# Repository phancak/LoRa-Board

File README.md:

# STM32WL55CCU6 LoRa Expansion Board  

## 📑 Quick Access
* [**📂 View Project Schematics (PDF)**](./Schematics/LoRa_Board_Schematics.pdf)

## Overview  
This project features a **LoRa expansion board** based on the **STM32WL55CCU6 MCU**, designed to provide long-range, low-power wireless communication for embedded systems. With support for **I2C**, **UART**, and **SPI** communication interfaces, this board is ideal for integrating **LoRa** functionality into larger projects, enabling **reliable, long-range data transmission** in applications like **IoT** and **industrial automation**. The STM32WL55CCU6 offers an energy-efficient solution for **wireless connectivity** in remote or challenging environments.

## Features  
- **STM32WL55CCU6 MCU** – Ultra-low-power, LoRa-capable microcontroller  
- **LoRa Communication** – Long-range, low-power wireless protocol  
- **I2C, UART, SPI Interfaces** – Multiple communication options for flexibility  
- **Low Power Operation** – Ideal for battery-operated and remote applications  
- **Compact Design** – Easily integratable into various embedded systems  

## Applications  
- **IoT Networks** – Connecting sensors and devices over long distances  
- **Smart Agriculture** – Wireless communication for monitoring systems  
- **Asset Tracking** – Real-time location data transmission in logistics  
- **Industrial Automation** – Reliable wireless control and monitoring systems  

## Getting Started  
### Hardware Requirements  
- STM32WL55CCU6 LoRa Expansion Board  
- Host MCU (e.g., STM32, ESP32, Raspberry Pi, etc.)  
- Power Supply (3.3V)  
- USB-to-Serial Debugging Tools  

### Software Requirements  
- **STM32CubeIDE** – Development environment for firmware  
- **LoRaWAN Libraries** – LoRa communication protocol support  
- **ST-Link or J-Link** – Debugging and flashing tools  

## Setup & Usage  
1. **Power the Board** – Provide 3.3V to the board.  
2. **Connect to Host MCU** – Use I2C, UART, or SPI to interface with the board.  
3. **Flash Firmware** – Upload firmware for LoRa communication.  
4. **Start Transmitting** – Send and receive long-range data using LoRa.

## Repository Structure  
/Hardware - PCB schematics and design files
/Schematic - Circuit diagrams (PDF, KiCad, Altium, etc.)
/PCB - Board layout files (Gerber, BOM, assembly files)

## Future Enhancements  
- 🔹 **Advanced Power Management** – Further optimization for ultra-low-power operation  
- 🔹 **Multi-Channel Support** – Enable simultaneous communication across multiple LoRa channels  
- 🔹 **Secure Communication** – Integrate encryption for data security  

## License  
This project is open-source under the **MIT License**.

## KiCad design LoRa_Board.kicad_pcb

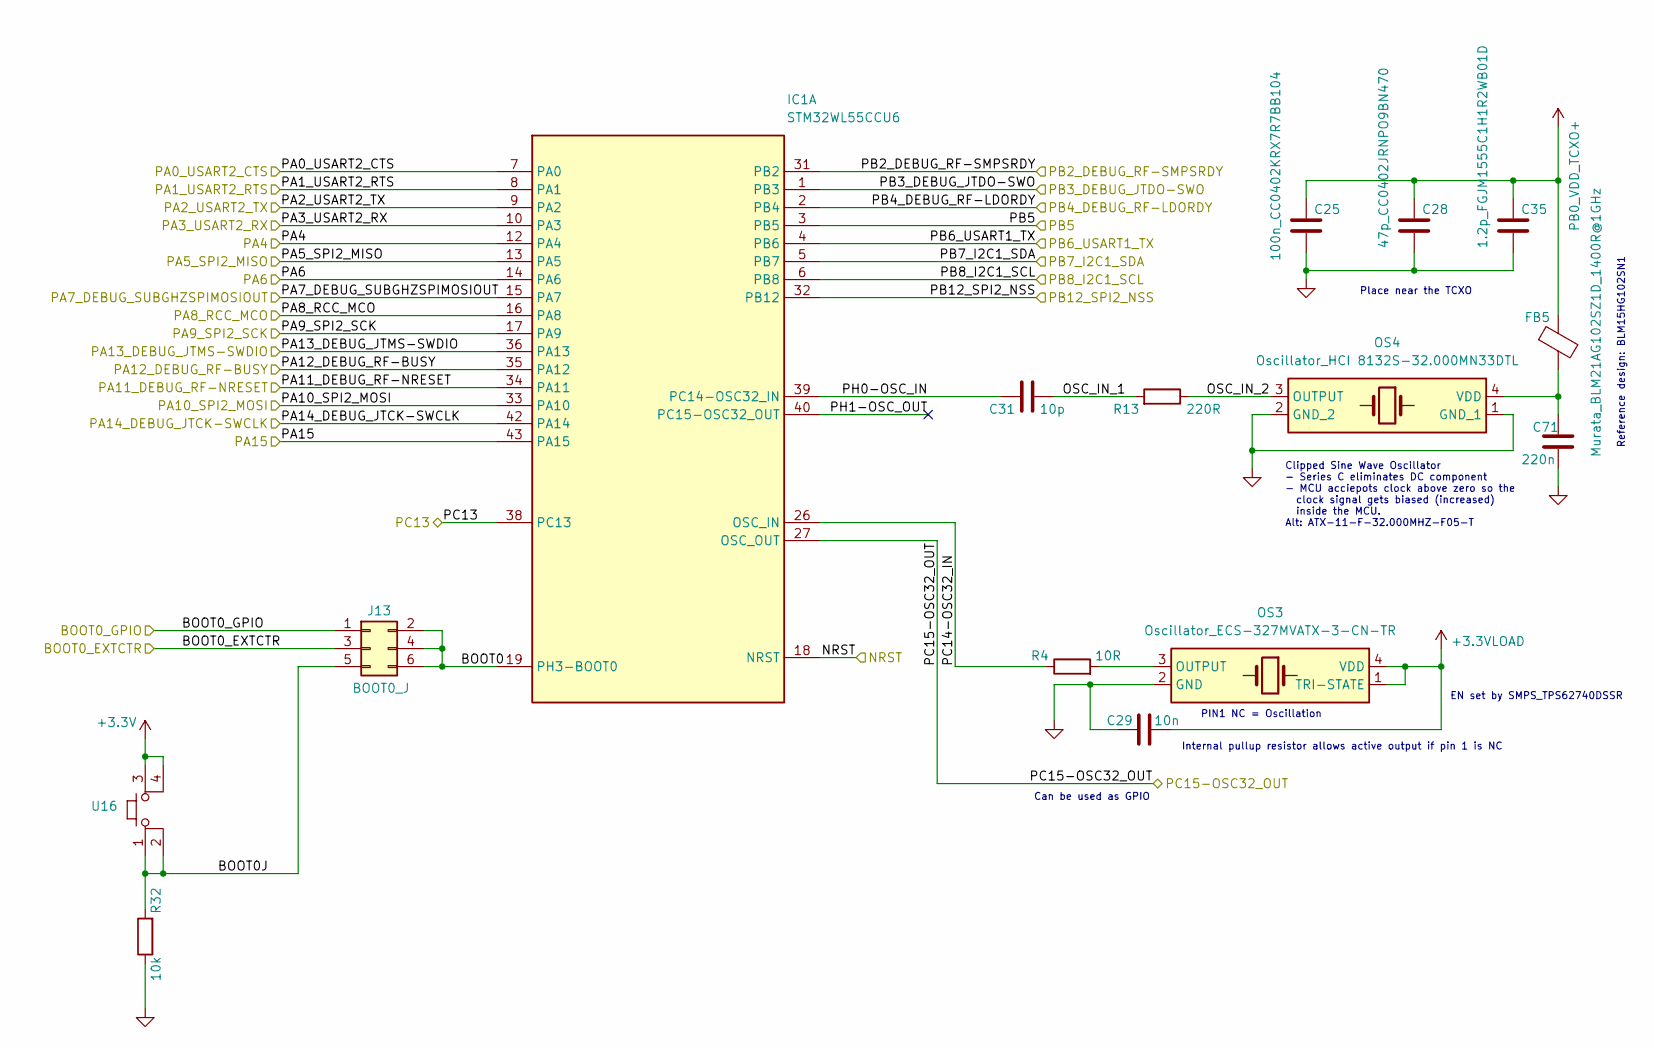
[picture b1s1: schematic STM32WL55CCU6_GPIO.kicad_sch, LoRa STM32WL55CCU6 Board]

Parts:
C25: 100n_CC0402KRX7R7BB104; C_0603_1608Metric
C28: 47p_CC0402JRNPO9BN470; C_0603_1608Metric
C29: 10n; C_0603_1608Metric
C31: 10p; C_0603_1608Metric
C35: 1.2p_FGJM1555C1H1R2WB01D; C_0603_1608Metric
C71: 220n; C_0603_1608Metric
FB5: Murata_BLM21AG102SZ1D_1400R@1GHz; C_0805_2012Metric
IC1: STM32WL55CCU6; STM32WL55CCU6_QFN50P700X700X65-49N-D; Manufacturer_Part_Number STM32WL55CCU6; Mouser Part Number 511-STM32WL55CCU6
J13: BOOT0_J; PinHeader_2x03_P2.54mm_Vertical
OS3: Oscillator_ECS-327MVATX-3-CN-TR; Crystal_SMD_3225-4Pin_3.2x2.5mm; Mouser Part Number 520-327MVATX-3-CNT
OS4: Oscillator_HCI 8132S-32.000MN33DTL; Crystal_SMD_3225-4Pin_3.2x2.5mm; Mouser Part Number 520-TXO32CSMV320ANTR
R4: 10R; R_0603_1608Metric
R13: 220R; R_0603_1608Metric
R32: 10k; R_0805_2012Metric
U16: Button_SKSCLCE010

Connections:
+3.3V: U16.3, U16.4; also elsewhere on the board
+3.3VLOAD: C29.2, OS3.1 (TRI-STATE), OS3.4 (VDD); also elsewhere on the board
/Interfaces/I2C_SCL_HDR_0: IC1.6 (PB8); also elsewhere on the board
/Interfaces/I2C_SDA_HDR_0: IC1.5 (PB7); also elsewhere on the board
/Interfaces/I/O_HDR0: J13.1; also elsewhere on the board
/Interfaces/I/O_HDR1: IC1.8 (PA1); also elsewhere on the board
/Interfaces/I/O_HDR2: IC1.15 (PA7); also elsewhere on the board
/Interfaces/I/O_HDR3: IC1.16 (PA8); also elsewhere on the board
/Interfaces/I/O_HDR4: IC1.43 (PA15); also elsewhere on the board
/Interfaces/I/O_HDR5: IC1.38 (PC13); also elsewhere on the board
/Interfaces/I/O_HDR6: IC1.34 (PA11); also elsewhere on the board
/Interfaces/I/O_HDR7: IC1.31 (PB2); also elsewhere on the board
/Interfaces/I/O_HDR8: IC1.35 (PA12); also elsewhere on the board
/Interfaces/I/O_HDR9: IC1.2 (PB4); also elsewhere on the board
/Interfaces/I/O_HDR10: IC1.7 (PA0); also elsewhere on the board
/Interfaces/SPI_CLK: IC1.17 (PA9); also elsewhere on the board
/Interfaces/SPI_CS: IC1.32 (PB12); also elsewhere on the board
/Interfaces/SPI_MISO: IC1.13 (PA5); also elsewhere on the board
/Interfaces/SPI_MOSI: IC1.33 (PA10); also elsewhere on the board
/Interfaces/UART1_TX/RX: IC1.4 (PB6); also elsewhere on the board
/Power_Management/BFR_RST: IC1.18 (NRST); also elsewhere on the board
/Power_Management/CTRL: IC1.3 (PB5); also elsewhere on the board
/STM32WL55CCU6_GPIO/BOOT0: IC1.19 (PH3-BOOT0), J13.2, J13.4, J13.6
/STM32WL55CCU6_GPIO/BOOT0J: J13.5, R32.2, U16.1, U16.2
/STM32WL55CCU6_GPIO/BOOT0_EXTCTR: J13.3; also elsewhere on the board
/STM32WL55CCU6_GPIO/OSC_IN_1: C31.1, R13.2
/STM32WL55CCU6_GPIO/OSC_IN_2: OS4.3 (OUTPUT), R13.1
/STM32WL55CCU6_GPIO/PA2_USART2_TX: IC1.9 (PA2); also elsewhere on the board
/STM32WL55CCU6_GPIO/PA3_USART2_RX: IC1.10 (PA3); also elsewhere on the board
/STM32WL55CCU6_GPIO/PA4: IC1.12 (PA4); also elsewhere on the board
/STM32WL55CCU6_GPIO/PA6: IC1.14 (PA6); also elsewhere on the board
/STM32WL55CCU6_GPIO/PA13_DEBUG_JTMS-SWDIO: IC1.36 (PA13); also elsewhere on the board
/STM32WL55CCU6_GPIO/PA14_DEBUG_JTCK-SWCLK: IC1.42 (PA14); also elsewhere on the board
/STM32WL55CCU6_GPIO/PB3_DEBUG_JTDO-SWO: IC1.1 (PB3); also elsewhere on the board
/STM32WL55CCU6_GPIO/PC14-OSC32_IN: IC1.26 (OSC_IN), R4.1
/STM32WL55CCU6_GPIO/PC15-OSC32_OUT: IC1.27 (OSC_OUT); also elsewhere on the board
/STM32WL55CCU6_GPIO/PH0-OSC_IN: C31.2, IC1.39 (PC14-OSC32_IN)
/STM32WL55CCU6_GPIO/PH1-OSC_OUT: IC1.40 (PC15-OSC32_OUT)
GND: C25.2, C28.2, C29.1, C35.2, C71.1, OS3.2 (GND), OS4.1 (GND_1), OS4.2 (GND_2), R32.1; also elsewhere on the board
unnamed: OS3.3 (OUTPUT), R4.2
unnamed: C71.2, FB5.2, OS4.4 (VDD)
PB0_VDD_TCXO+: C25.1, C28.1, C35.1, FB5.1; also elsewhere on the board

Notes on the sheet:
Internal pullup resistor allows active output if pin 1 is NC
PIN1 NC = Oscillation
Clipped Sine Wave Oscillator - Series C eliminates DC component - MCU acciepots clock above zero so the clock signal gets biased (increased) inside the MCU. Alt: ATX-11-F-32.000MHZ-F05-T
EN set by SMPS_TPS62740DSSR
Place near the TCXO
Can be used as GPIO
Reference design: BLM15HG102SN1

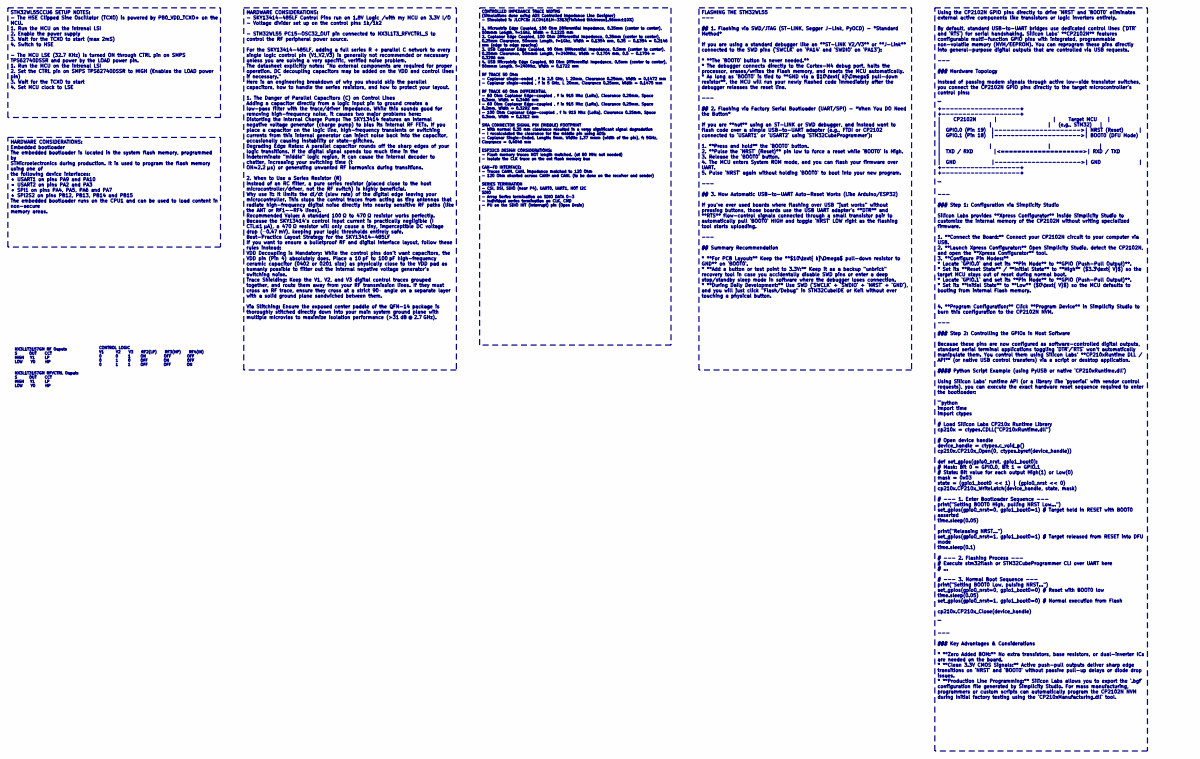
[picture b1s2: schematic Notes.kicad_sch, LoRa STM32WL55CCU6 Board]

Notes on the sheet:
CONTROL LOGIC V1 V2 V3 RF2(LP) RF3(HP) RF4(IN) 0 0 1 ON OFF OFF 0 1 0 OFF ON OFF 0 1 1 OFF OFF ON
NX3L1T3157GM RF Ouputs S OUT CCT HIGH Y1 LP LOW Y0 HP
NX3L1T3157GM RFVCTRL Ouputs S OUT CCT HIGH Y1 LP LOW Y0 HP
FLASHING THE STM32WL55 --- ## 1. Flashing via SWD/JTAG (ST-LINK, Segger J-Link, PyOCD) - *Standard Method* If you are using a standard debugger like an **ST-LINK V2/V3** or **J-Link** connected to the SWD pins (`SWCLK` on `PA14` and `SWDIO` on `PA13`): * **The `BOOT0` button is never needed.** * Th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
Using the CP2102N GPIO pins directly to drive `NRST` and `BOOT0` eliminates external active components like transistors or logic inverters entirely. By default, standard USB-to-UART bridges use dedicated control lines (`DTR` and `RTS`) for serial handshaking. Silicon Labs' **CP2102N** features conf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
CONTROLLED IMPEDANCE TRACE WIDTHS (Simulations done using ADS Controlled Impedance Line Designer) - Simulated is JLCPCB: JLC04161H-3313(Finished thickness1.56mm±10%) 1. Microstrip Edge Coupled, 100 Ohm Differential Impedance, 0.35mm (center to center), 50mmm Length, f=1Ghz, Width = 0.1225 mm 2. Cop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
HARDWARE CONSIDERATIONS: - SKY13414-485LF Control Pins run on 1.8V Logic /with my MCU on 3.3V I/O - Voltage divider set up on the control pins 1k/1k2 - STM32WL55 PC15-OSC32_OUT pin connected to NX3L1T3_RFVCTRL_S to control the RF peripheral power source. For the SKY13414-485LF, adding a full series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
STM32WL55CCU6 SETUP NOTES: - The HSE Clipped Sine Oscillator (TCXO) is powered by PB0_VDD_TCXO+ on the MCU. 1. Run the MCU on the intrenal LSI 2. Enable the power supply 3. Wait for the TCXO to start (max 2mS) 4. Switch to HSE - The MCU LSE (32.7 KHz) is turned ON through CTRL pin on SMPS TPS62740D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
HARDWARE CONSIDERATIONS: Embedded bootloader The embedded bootloader is located in the system flash memory, programmed by STMicroelectronics during production. It is used to program the flash memory using one of the following device interfaces: • USART1 on pins PA9 and PA10 • USART2 on pins PA2 and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

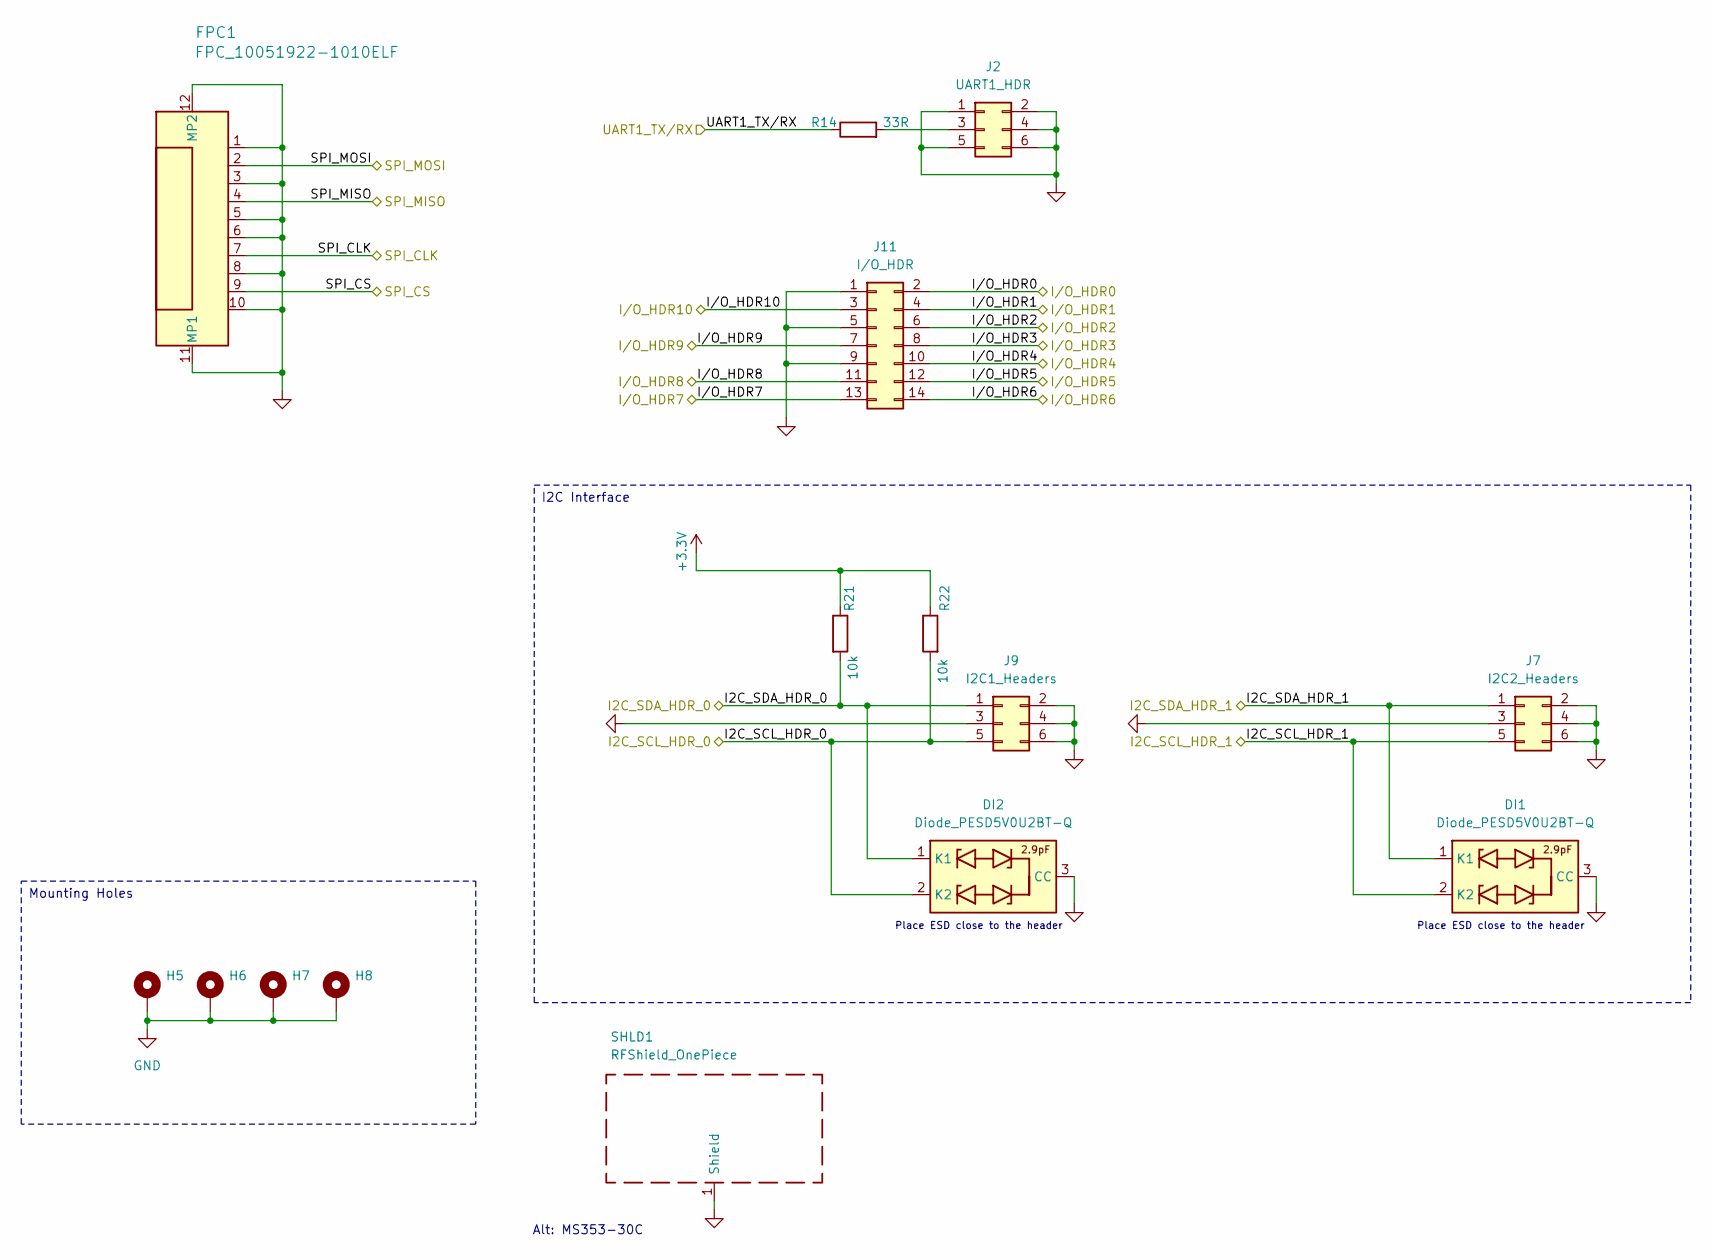
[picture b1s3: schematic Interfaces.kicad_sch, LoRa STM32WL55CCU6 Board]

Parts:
DI1, DI2: Diode_PESD5V0U2BT-Q; SOT-23; Manufacturer_Part_Number BZX84C6V2-7-F; Mouser Part Number 621-BZX84C6V2-F
FPC1: FPC_10051922-1010ELF; FPC_10051922_1010
H5, H6, H7, H8: MountingHole_Pad; MountingHole_3.2mm_M3_Pad
J2: UART1_HDR; PinHeader_2x03_P2.54mm_Horizontal_Court
J7: I2C2_Headers; PinHeader_2x03_P2.54mm_Horizontal_Court
J9: I2C1_Headers; PinHeader_2x03_P2.54mm_Horizontal_Court
J11: I/O_HDR; PinHeader_2x07_P2.54mm_Horizontal
R14: 33R; R_0603_1608Metric
R21, R22: 10k; R_0805_2012Metric
SHLD1: RFShield_OnePiece; RFSHIELD_MS353-30F

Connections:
+3.3V: R21.1, R22.1; also elsewhere on the board
/Interfaces/I2C_SCL_HDR_0: DI1.2 (K2), DI2.2 (K2), J7.5, J9.5, R22.2; also elsewhere on the board
/Interfaces/I2C_SDA_HDR_0: DI1.1 (K1), DI2.1 (K1), J7.1, J9.1, R21.2; also elsewhere on the board
/Interfaces/I/O_HDR0: J11.2; also elsewhere on the board
/Interfaces/I/O_HDR1: J11.4; also elsewhere on the board
/Interfaces/I/O_HDR2: J11.6; also elsewhere on the board
/Interfaces/I/O_HDR3: J11.8; also elsewhere on the board
/Interfaces/I/O_HDR4: J11.10; also elsewhere on the board
/Interfaces/I/O_HDR5: J11.12; also elsewhere on the board
/Interfaces/I/O_HDR6: J11.14; also elsewhere on the board
/Interfaces/I/O_HDR7: J11.13; also elsewhere on the board
/Interfaces/I/O_HDR8: J11.11; also elsewhere on the board
/Interfaces/I/O_HDR9: J11.7; also elsewhere on the board
/Interfaces/I/O_HDR10: J11.3; also elsewhere on the board
/Interfaces/SPI_CLK: FPC1.7; also elsewhere on the board
/Interfaces/SPI_CS: FPC1.9; also elsewhere on the board
/Interfaces/SPI_MISO: FPC1.4; also elsewhere on the board
/Interfaces/SPI_MOSI: FPC1.2; also elsewhere on the board
/Interfaces/UART1_TX/RX: R14.1; also elsewhere on the board
GND: DI1.3 (CC), DI2.3 (CC), FPC1.1, FPC1.3, FPC1.5, FPC1.6, FPC1.8, FPC1.10, FPC1.11 (MP1), FPC1.12 (MP2), H5.1 (1_1), H6.1 (1_1), H7.1 (1_1), H8.1 (1_1), J2.1, J2.2, J2.4, J2.5, J2.6, J7.2, J7.3, J7.4, J7.6, J9.2, J9.3, J9.4, J9.6, J11.1, J11.5, J11.9, SHLD1.1 (Shield_1); also elsewhere on the board
unnamed: J2.3, R14.2

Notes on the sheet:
Place ESD close to the header
Alt: MS353-30C
I2C Interface
Mounting Holes

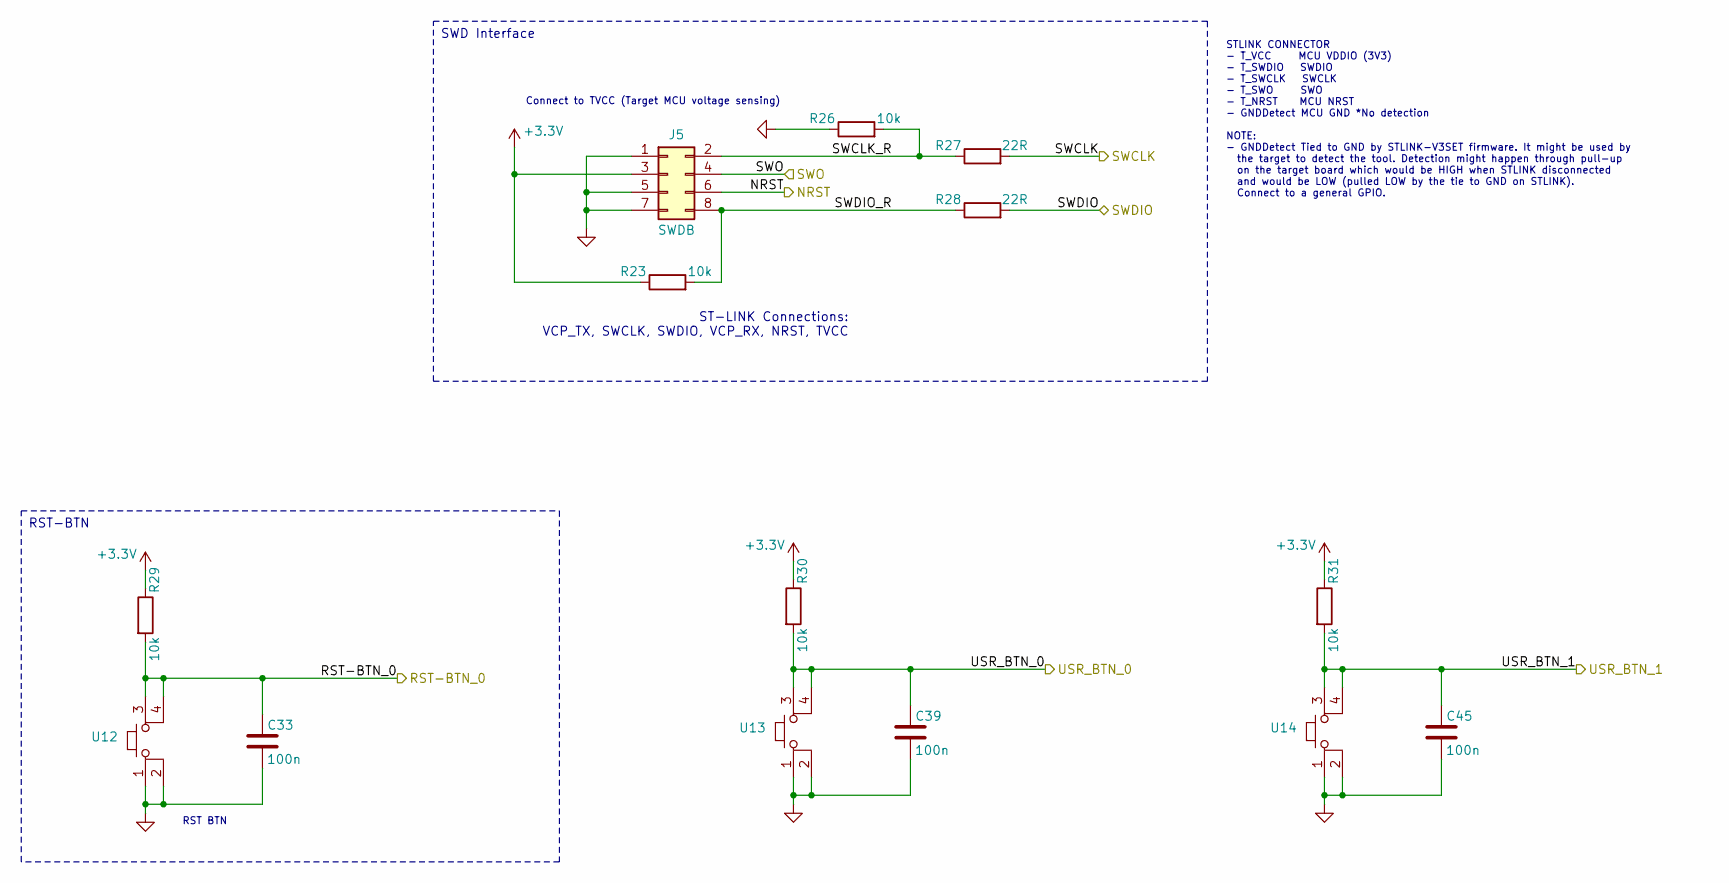
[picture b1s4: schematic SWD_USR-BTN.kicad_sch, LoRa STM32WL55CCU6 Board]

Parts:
C33, C39, C45: 100n; C_0603_1608Metric
J5: SWDB; PinHeader_2x04_P2.54mm_Horizontal
R23, R26: 10k; R_0603_1608Metric
R27, R28: 22R; R_0603_1608Metric
R29, R30, R31: 10k; R_0805_2012Metric
U12, U13, U14: Button_SKSCLCE010

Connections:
+3.3V: J5.3, R23.1, R29.1, R30.1, R31.1; also elsewhere on the board
/Interfaces/I/O_HDR6: C39.2, R30.2, U13.3, U13.4; also elsewhere on the board
/Interfaces/I/O_HDR7: C45.2, R31.2, U14.3, U14.4; also elsewhere on the board
/Power_Management/BFR_RST: C33.2, J5.6, R29.2, U12.3, U12.4; also elsewhere on the board
/STM32WL55CCU6_GPIO/PA13_DEBUG_JTMS-SWDIO: R28.2; also elsewhere on the board
/STM32WL55CCU6_GPIO/PA14_DEBUG_JTCK-SWCLK: R27.2; also elsewhere on the board
/STM32WL55CCU6_GPIO/PB3_DEBUG_JTDO-SWO: J5.4; also elsewhere on the board
/SWD_USR-BTN/SWCLK_R: J5.2, R26.2, R27.1
/SWD_USR-BTN/SWDIO_R: J5.8, R23.2, R28.1
GND: C33.1, C39.1, C45.1, J5.1, J5.5, J5.7, R26.1, U12.1, U12.2, U13.1, U13.2, U14.1, U14.2; also elsewhere on the board

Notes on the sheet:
Connect to TVCC (Target MCU voltage sensing)
STLINK CONNECTOR - T_VCC MCU VDDIO (3V3) - T_SWDIO SWDIO - T_SWCLK SWCLK - T_SWO SWO - T_NRST MCU NRST - GNDDetect MCU GND *No detection NOTE: - GNDDetect Tied to GND by STLINK-V3SET firmware. It might be used by the target to detect the tool. Detection might happen through pull-up on the target bo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
ST-LINK Connections: VCP_TX, SWCLK, SWDIO, VCP_RX, NRST, TVCC
RST BTN
RST-BTN
SWD Interface

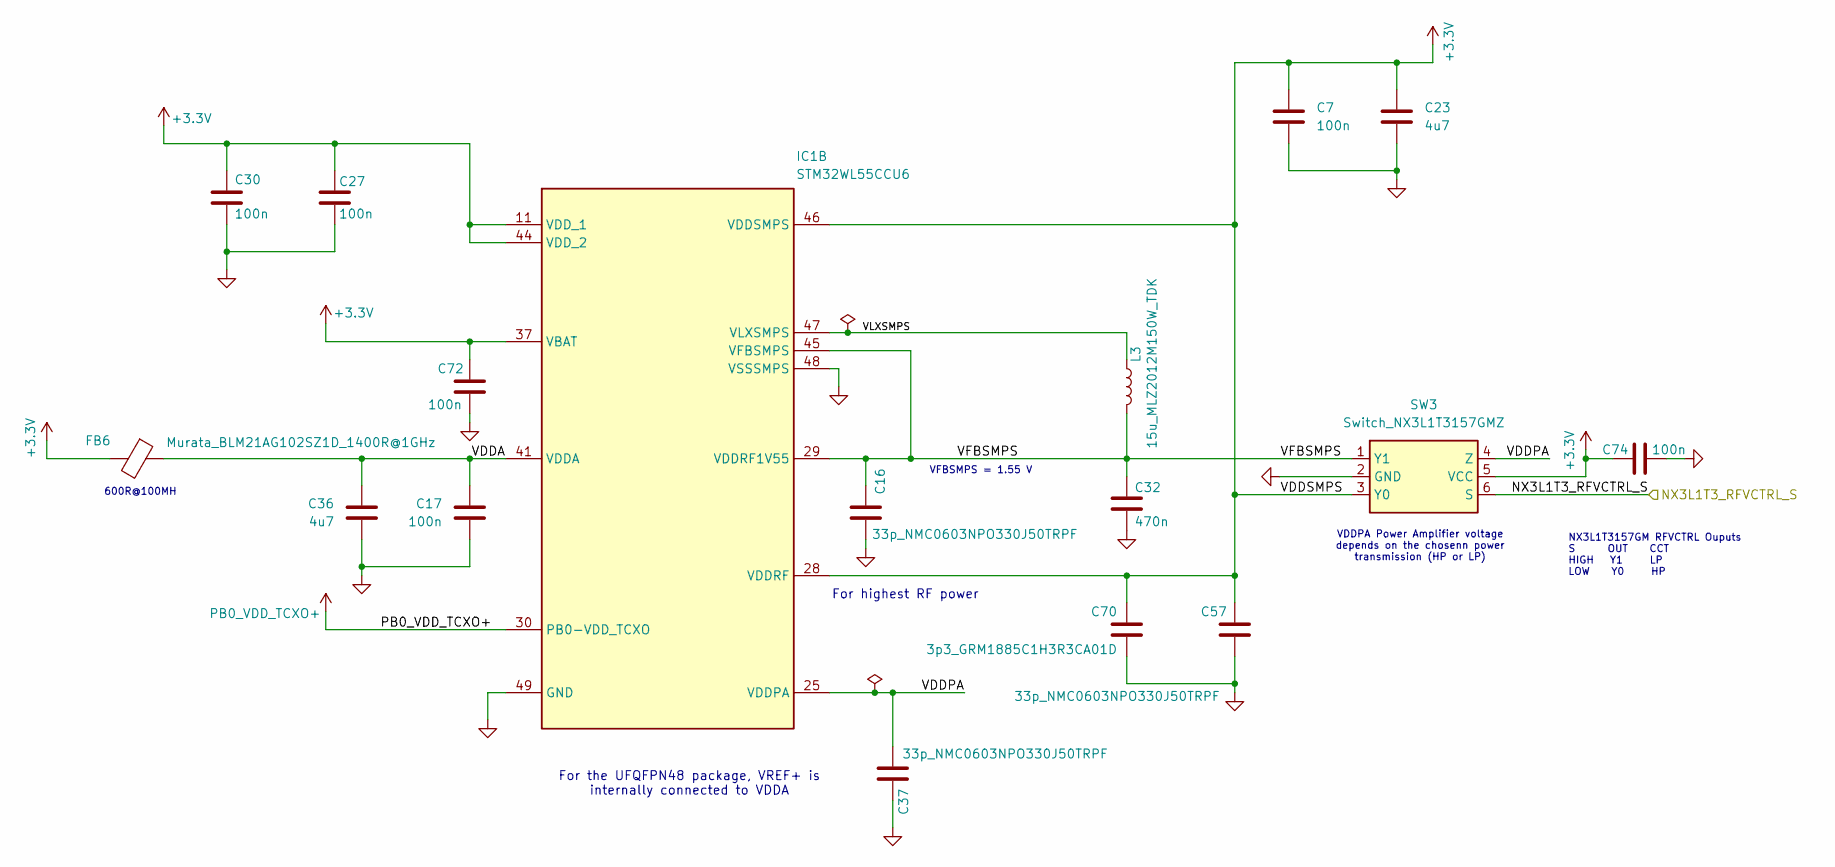
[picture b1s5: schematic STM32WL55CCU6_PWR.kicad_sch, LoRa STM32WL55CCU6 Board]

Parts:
C7, C17, C27, C30, C72, C74: 100n; C_0603_1608Metric
C16, C37, C57: 33p_NMC0603NPO330J50TRPF; C_0603_1608Metric
C23, C36: 4u7; C_0603_1608Metric
C32: 470n; C_0603_1608Metric
C70: 3p3_GRM1885C1H3R3CA01D; C_0603_1608Metric
FB6: Murata_BLM21AG102SZ1D_1400R@1GHz; C_0805_2012Metric
IC1: STM32WL55CCU6; STM32WL55CCU6_QFN50P700X700X65-49N-D; Manufacturer_Part_Number STM32WL55CCU6; Mouser Part Number 511-STM32WL55CCU6
L3: 15u_MLZ2012M150W_TDK; L_0805_2012Metric
SW3: Switch_NX3L1T3157GMZ; Switch_NX3L1T3157GM115; Mouser Part Number 771-NX3L1T3157GM115

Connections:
+3.3V: C7.1, C23.1, C27.1, C30.1, C57.1, C70.1, C72.1, C74.1, FB6.2, IC1.11 (VDD_1), IC1.28 (VDDRF), IC1.37 (VBAT), IC1.44 (VDD_2), IC1.46 (VDDSMPS), SW3.3 (Y0), SW3.5 (VCC); also elsewhere on the board
/STM32WL55CCU6_GPIO/PC15-OSC32_OUT: SW3.6 (S); also elsewhere on the board
/STM32WL55CCU6_PWR/VDDA: C17.1, C36.1, FB6.1, IC1.41 (VDDA)
/STM32WL55CCU6_PWR/VDDPA: C37.2, IC1.25 (VDDPA), SW3.4 (Z)
/STM32WL55CCU6_PWR/VFBSMPS: C16.2, C32.1, IC1.29 (VDDRF1V55), IC1.45 (VFBSMPS), L3.1, SW3.1 (Y1)
/STM32WL55CCU6_PWR/VLXSMPS: IC1.47 (VLXSMPS), L3.2
GND: C7.2, C16.1, C17.2, C23.2, C27.2, C30.2, C32.2, C36.2, C37.1, C57.2, C70.2, C72.2, C74.2, IC1.48 (VSSSMPS), IC1.49 (GND), SW3.2 (GND); also elsewhere on the board
PB0_VDD_TCXO+: IC1.30 (PB0-VDD_TCXO); also elsewhere on the board

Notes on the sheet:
600R@100MH
VFBSMPS = 1.55 V
VDDPA Power Amplifier voltage depends on the chosenn power transmission (HP or LP)
For the UFQFPN48 package, VREF+ is internally connected to VDDA
NX3L1T3157GM RFVCTRL Ouputs S OUT CCT HIGH Y1 LP LOW Y0 HP
For highest RF power

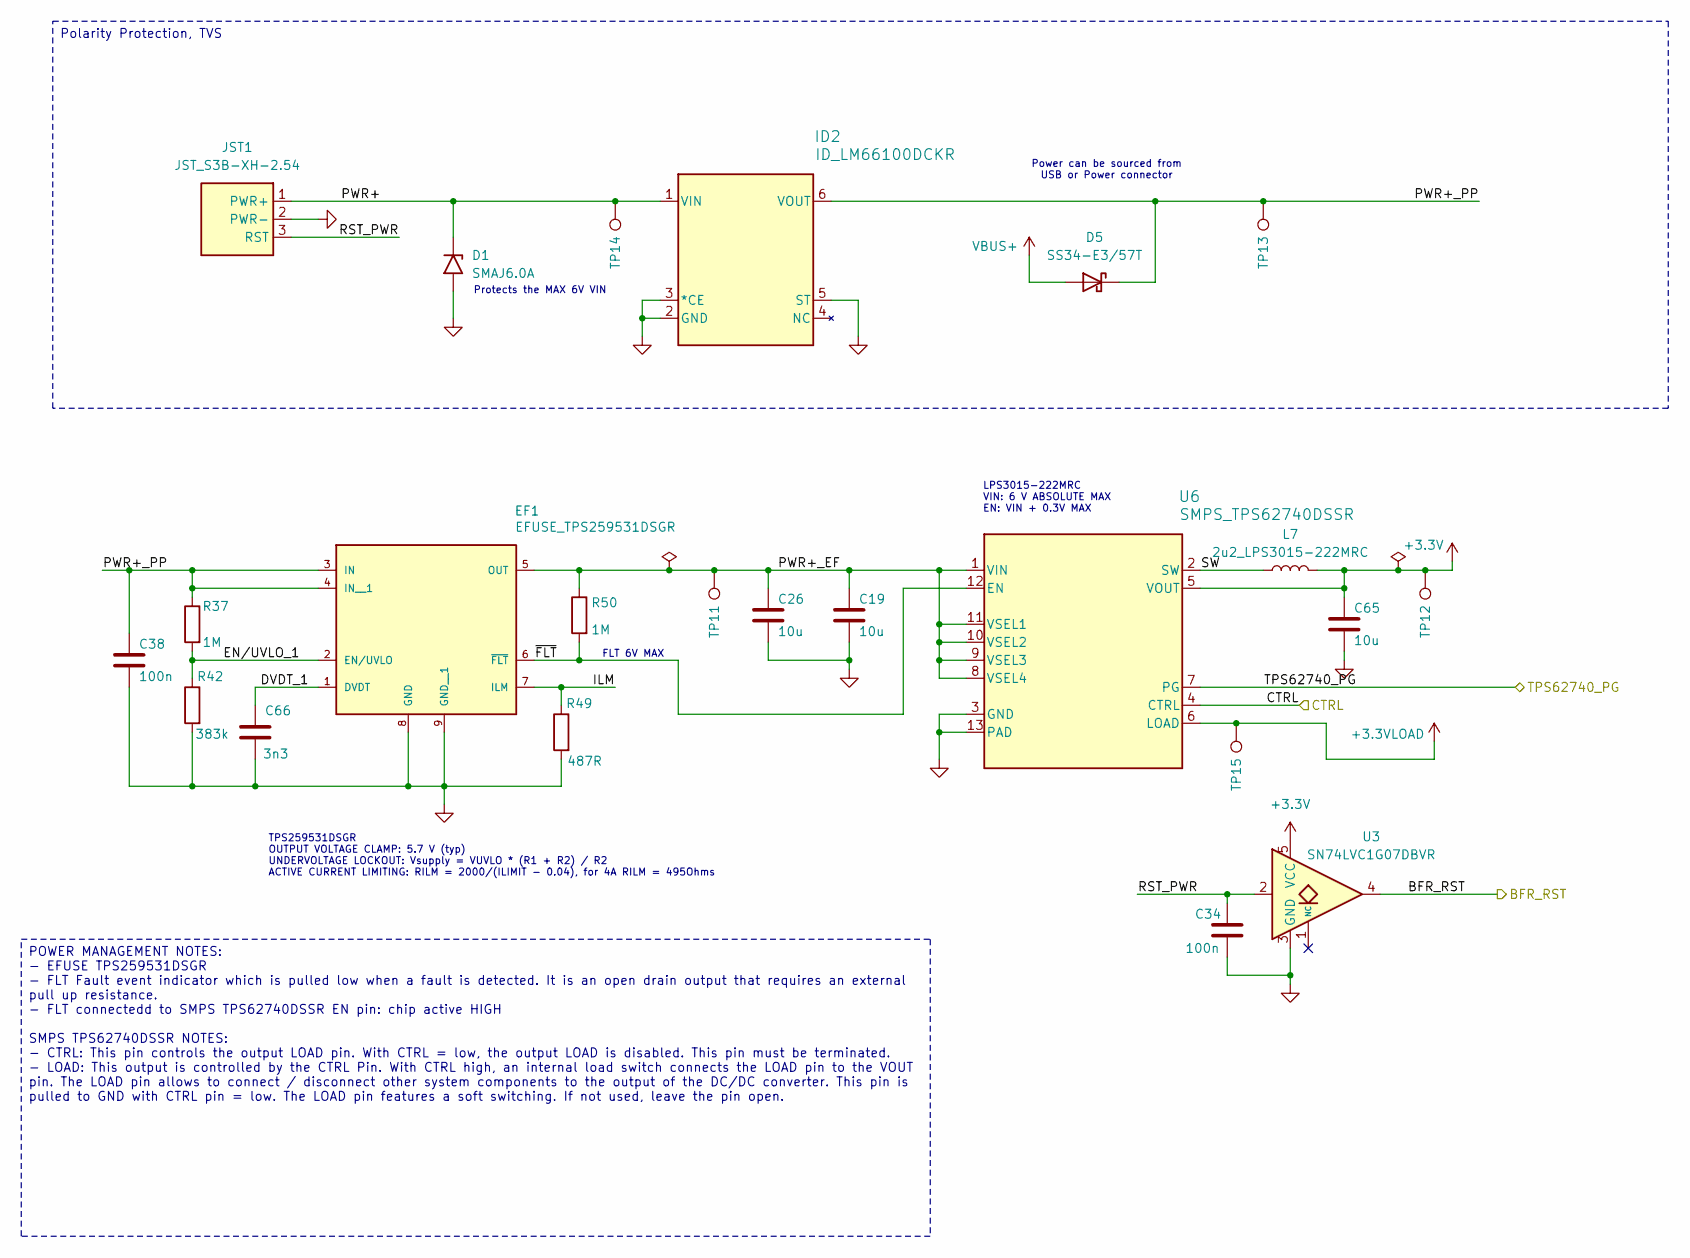
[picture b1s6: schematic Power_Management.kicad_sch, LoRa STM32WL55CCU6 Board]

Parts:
C19, C26, C65: 10u; C_0603_1608Metric
C34: 100n; C_0805_2012Metric
C38: 100n; C_0603_1608Metric
C66: 3n3; C_0603_1608Metric
D1: SMAJ6.0A; DO-214AC-2
D5: SS34-E3/57T; D_SMA
EF1: EFUSE_TPS259531DSGR; EF_TPS259531DSGR; PARTREV C
ID2: ID_LM66100DCKR
JST1: JST_S3B-XH-2.54; JST_S3B-XH-SHDRRA3W64P0X250_1X3_990X1150X610P; Mouser Part Number 306-S3BXHA1LFSN
L7: 2u2_LPS3015-222MRC; L_Coilcraft_LPS3010
R37, R50: 1M; R_0603_1608Metric
R42: 383k; R_0603_1608Metric
R49: 487R; R_0603_1608Metric
TP11, TP12, TP13, TP14, TP15: TestPoint; TestPoint_Pad_1.5x1.5mm
U3: SN74LVC1G07DBVR; SOT-23-5
U6: SMPS_TPS62740DSSR

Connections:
+3.3V: C65.1, L7.2, TP12.1 (1_1), U3.5 (VCC), U6.5 (VOUT); also elsewhere on the board
+3.3VLOAD: TP15.1 (1_1), U6.6 (LOAD); also elsewhere on the board
/Power_Management/BFR_RST: U3.4; also elsewhere on the board
/Power_Management/CTRL: U6.4 (CTRL); also elsewhere on the board
/Power_Management/DVDT_1: C66.2, EF1.1 (DVDT)
/Power_Management/EN/UVLO_1: EF1.2 (EN/UVLO), R37.2, R42.1
/Power_Management/ILM: EF1.7 (ILM), R49.1
/Power_Management/PWR+: D1.1 (K), ID2.1 (VIN), JST1.1 (PWR+), TP14.1 (1_1)
/Power_Management/PWR+_EF: C19.1, C26.1, EF1.5 (OUT), R50.1, TP11.1 (1_1), U6.1 (VIN), U6.8 (VSEL4), U6.9 (VSEL3), U6.10 (VSEL2), U6.11 (VSEL1)
/Power_Management/PWR+_PP: C38.1, D5.1 (K), EF1.3 (IN), EF1.4 (IN__1), ID2.6 (VOUT), R37.1, TP13.1 (1_1)
/Power_Management/RST_PWR: C34.1, JST1.3 (RST), U3.2
/Power_Management/SW: L7.1, U6.2 (SW)
/Power_Management/TPS62740_PG: U6.7 (PG)
/Power_Management/~FLT: EF1.6 (~FLT), R50.2, U6.12 (EN)
GND: C19.2, C26.2, C34.2, C38.2, C65.2, C66.1, D1.2 (A), EF1.8 (GND), EF1.9 (GND__1), ID2.2 (GND), ID2.3 (*CE), ID2.5 (ST), JST1.2 (PWR-), R42.2, R49.2, U3.3 (GND), U6.3 (GND), U6.13 (PAD); also elsewhere on the board
VBUS+: D5.2 (A); also elsewhere on the board

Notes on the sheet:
TPS259531DSGR OUTPUT VOLTAGE CLAMP: 5.7 V (typ) UNDERVOLTAGE LOCKOUT: Vsupply = VUVLO * (R1 + R2) / R2 ACTIVE CURRENT LIMITING: RILM = 2000/(ILIMIT - 0.04), for 4A RILM = 495Ohms
FLT 6V MAX
Power can be sourced from USB or Power connector
Protects the MAX 6V VIN
LPS3015-222MRC VIN: 6 V ABSOLUTE MAX EN: VIN + 0.3V MAX
POWER MANAGEMENT NOTES: - EFUSE TPS259531DSGR - FLT Fault event indicator which is pulled low when a fault is detected. It is an open drain output that requires an external pull up resistance. - FLT connectedd to SMPS TPS62740DSSR EN pin: chip active HIGH SMPS TPS62740DSSR NOTES: - CTRL: This pin c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
Polarity Protection, TVS

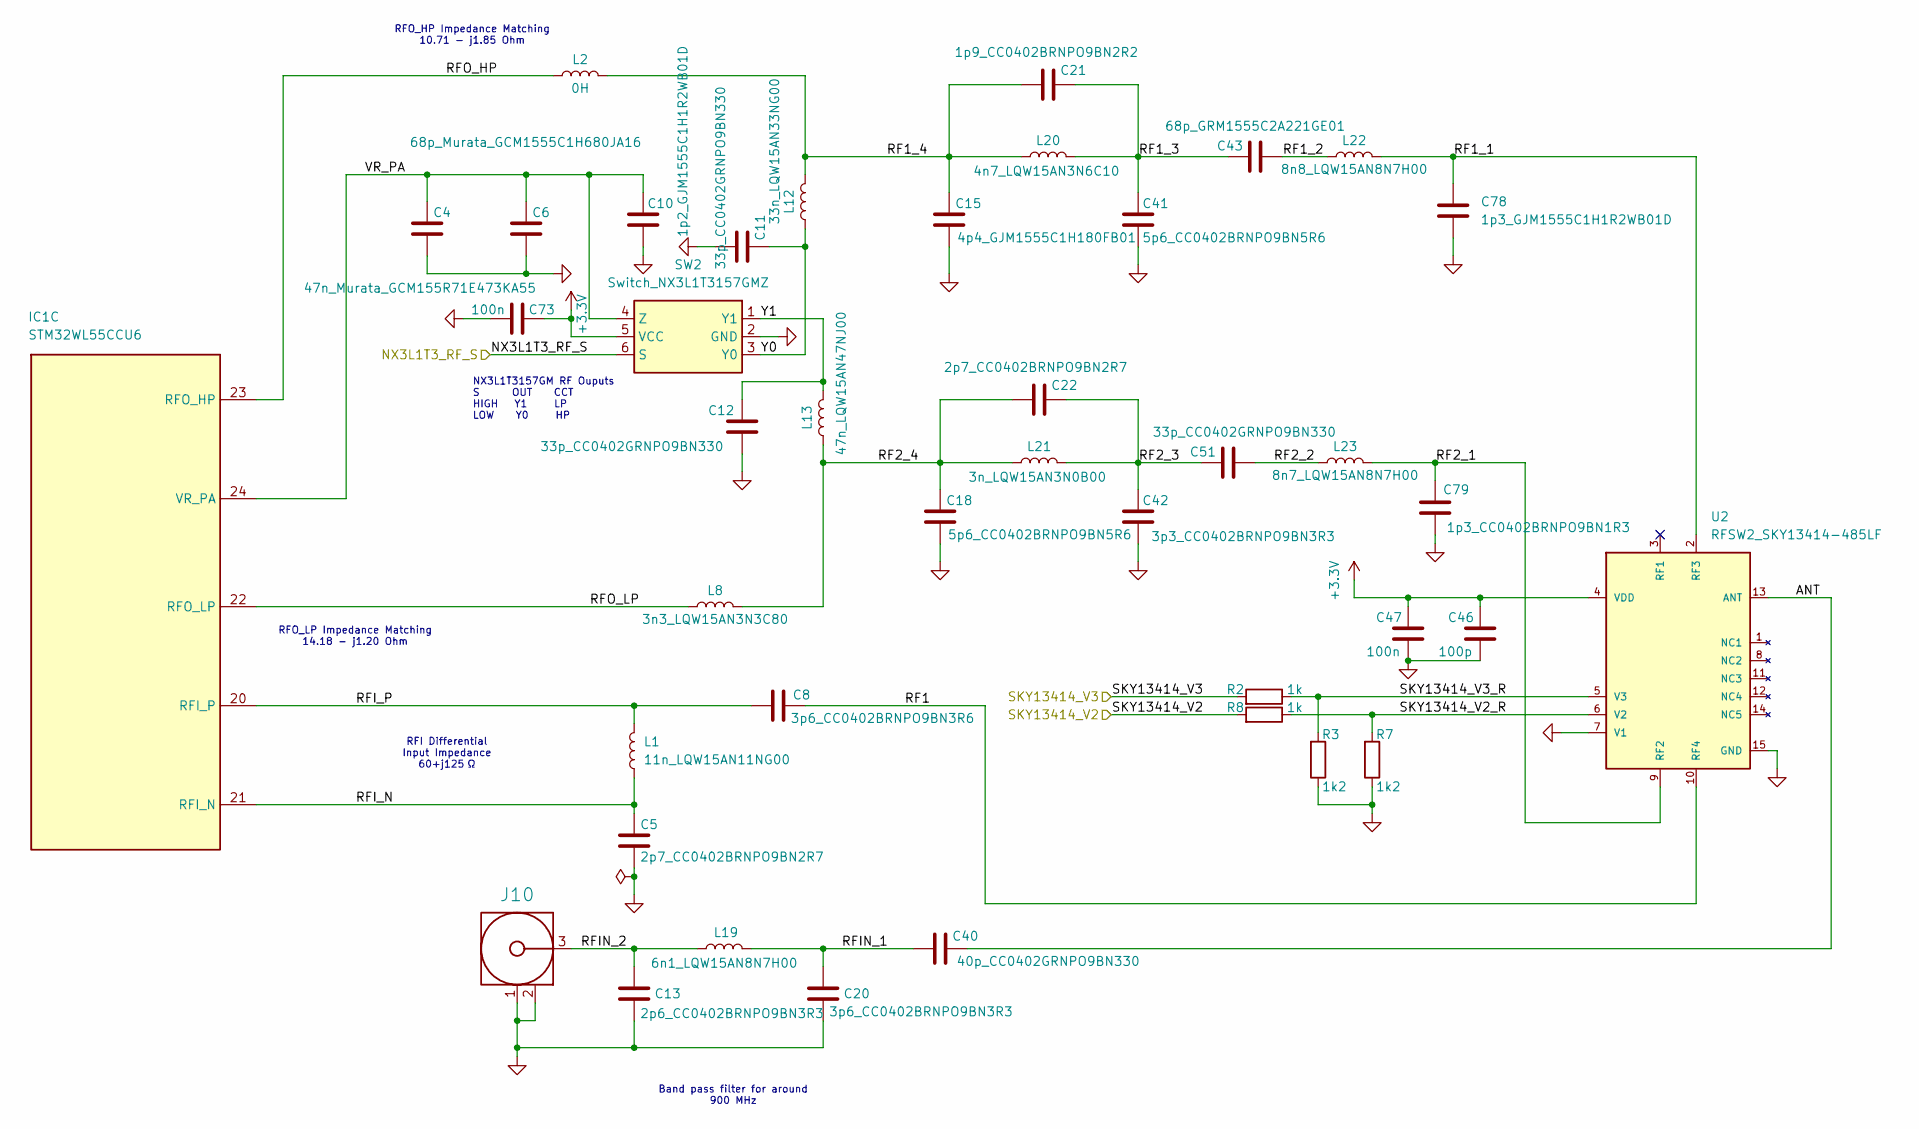
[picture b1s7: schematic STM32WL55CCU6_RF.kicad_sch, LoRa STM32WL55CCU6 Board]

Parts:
C4: 47n_Murata_GCM155R71E473KA55; C_0603_1608Metric
C5, C22: 2p7_CC0402BRNPO9BN2R7; C_0603_1608Metric
C6: 68p_Murata_GCM1555C1H680JA16; C_0603_1608Metric
C8: 3p6_CC0402BRNPO9BN3R6; C_0603_1608Metric
C10: 1p2_GJM1555C1H1R2WB01D; C_0603_1608Metric
C11, C12, C51: 33p_CC0402GRNPO9BN330; C_0603_1608Metric
C13: 2p6_CC0402BRNPO9BN3R3; C_0603_1608Metric
C15: 4p4_GJM1555C1H180FB01; C_0603_1608Metric
C18, C41: 5p6_CC0402BRNPO9BN5R6; C_0603_1608Metric
C20: 3p6_CC0402BRNPO9BN3R3; C_0603_1608Metric
C21: 1p9_CC0402BRNPO9BN2R2; C_0603_1608Metric
C40: 40p_CC0402GRNPO9BN330; C_0603_1608Metric
C42: 3p3_CC0402BRNPO9BN3R3; C_0603_1608Metric
C43: 68p_GRM1555C2A221GE01; C_0603_1608Metric
C46: 100p; C_0603_1608Metric
C47, C73: 100n; C_0603_1608Metric
C78: 1p3_GJM1555C1H1R2WB01D; C_0603_1608Metric
C79: 1p3_CC0402BRNPO9BN1R3; C_0603_1608Metric
IC1: STM32WL55CCU6; STM32WL55CCU6_QFN50P700X700X65-49N-D; Manufacturer_Part_Number STM32WL55CCU6; Mouser Part Number 511-STM32WL55CCU6
J10: SMA PCB END LAUNCH JACK ROUND PO; SMA Clip Mount Adapter (top); Manufacturer Part Number 60311002111526
L1: 11n_LQW15AN11NG00; L_0603_1608Metric_Pad1.05x0.95mm_HandSolder
L2: 0H; L_0603_1608Metric_Pad1.05x0.95mm_HandSolder
L8: 3n3_LQW15AN3N3C80; L_0603_1608Metric
L12: 33n_LQW15AN33NG00; L_0603_1608Metric
L13: 47n_LQW15AN47NJ00; L_0603_1608Metric
L19: 6n1_LQW15AN8N7H00; L_0603_1608Metric
L20: 4n7_LQW15AN3N6C10; L_0603_1608Metric
L21: 3n_LQW15AN3N0B00; L_0603_1608Metric
L22: 8n8_LQW15AN8N7H00; L_0603_1608Metric
L23: 8n7_LQW15AN8N7H00; L_0603_1608Metric
R2, R8: 1k; R_0603_1608Metric
R3, R7: 1k2; R_0603_1608Metric
SW2: Switch_NX3L1T3157GMZ; Switch_NX3L1T3157GM115; Mouser Part Number 771-NX3L1T3157GM115
U2: RFSW2_SKY13414-485LF; PARTREV November 23, 2016

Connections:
+3.3V: C46.1, C47.1, C73.1, SW2.5 (VCC), U2.4 (VDD); also elsewhere on the board
/STM32WL55CCU6_GPIO/PA4: R8.2; also elsewhere on the board
/STM32WL55CCU6_GPIO/PA6: R2.2, SW2.6 (S); also elsewhere on the board
/STM32WL55CCU6_RF/ANT: C40.2, U2.13 (ANT)
/STM32WL55CCU6_RF/RF1: C8.2, U2.10 (RF4)
/STM32WL55CCU6_RF/RF1_1: C78.2, L22.2, U2.2 (RF3)
/STM32WL55CCU6_RF/RF1_2: C43.2, L22.1
/STM32WL55CCU6_RF/RF1_3: C21.2, C41.2, C43.1, L20.2
/STM32WL55CCU6_RF/RF1_4: C15.2, C21.1, L2.2, L12.2, L20.1
/STM32WL55CCU6_RF/RF2_1: C79.2, L23.2, U2.9 (RF2)
/STM32WL55CCU6_RF/RF2_2: C51.2, L23.1
/STM32WL55CCU6_RF/RF2_3: C22.2, C42.2, C51.1, L21.2
/STM32WL55CCU6_RF/RF2_4: C18.2, C22.1, L8.2, L13.1, L21.1
/STM32WL55CCU6_RF/RFIN_1: C20.2, C40.1, L19.2
/STM32WL55CCU6_RF/RFIN_2: C13.2, J10.3 (Signal), L19.1
/STM32WL55CCU6_RF/RFI_N: C5.2, IC1.21 (RFI_N), L1.1
/STM32WL55CCU6_RF/RFI_P: C8.1, IC1.20 (RFI_P), L1.2
/STM32WL55CCU6_RF/RFO_HP: IC1.23 (RFO_HP), L2.1
/STM32WL55CCU6_RF/RFO_LP: IC1.22 (RFO_LP), L8.1
/STM32WL55CCU6_RF/SKY13414_V2_R: R7.2, R8.1, U2.6 (V2)
/STM32WL55CCU6_RF/SKY13414_V3_R: R2.1, R3.2, U2.5 (V3)
/STM32WL55CCU6_RF/VR_PA: C4.1, C6.1, C10.1, IC1.24 (VR_PA), SW2.4 (Z)
/STM32WL55CCU6_RF/Y0: C11.2, L12.1, SW2.3 (Y0)
/STM32WL55CCU6_RF/Y1: C12.2, L13.2, SW2.1 (Y1)
GND: C4.2, C5.1, C6.2, C10.2, C11.1, C12.1, C13.1, C15.1, C18.1, C20.1, C41.1, C42.1, C46.2, C47.2, C73.2, C78.1, C79.1, J10.1 (GND), J10.2 (GND), R3.1, R7.1, SW2.2 (GND), U2.7 (V1), U2.15 (GND); also elsewhere on the board

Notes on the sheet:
NX3L1T3157GM RF Ouputs S OUT CCT HIGH Y1 LP LOW Y0 HP
RFO_LP Impedance Matching 14.18 - j1.20 Ohm
RFI Differential Input Impedance 60+j125 Ω
RFO_HP Impedance Matching 10.71 - j1.85 Ohm
Band pass filter for around 900 MHz
